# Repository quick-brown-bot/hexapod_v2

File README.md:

# Hexapod

An ESP32-powered hexapod robot built as a long-term robotics and embedded systems project.

The goal is not just to make a robot walk, but to learn and at the same time build a platform that is easy to experiment with, tune, and extend. Most robot behavior is configurable at runtime, control inputs are transport-independent, and the motion stack is organized into separated components.

The project combines firmware, hardware design, and system documentation in a single repository.

> 6 legs, 18 servos, ESP32 mainboard, distributed RP2040 leg controllers over
> an RS485 bus, per-servo current sensing.

This is a continuation of the original [Hexabot](https://github.com/quick-brown-bot/hexapod) project, developed here in
[`hexapod_v2`](https://github.com/quick-brown-bot/hexapod_v2). It differs from
the original mainly in electronics architecture — distributed RP2040 leg
controllers over RS485 instead of a single ESP32 driving all servos directly —
and adds new features such as per-servo current sensing.

---

## What Is In This Repository

The repository contains software and hardware assets used to develop and validate the robot.

```text
firmware/
├── mainboard/             ESP32 mainboard firmware (RS485 master)
├── leg/                   RP2040 leg controller firmware
└── mainboard_rs485_test/  Standalone RS485 bring-up/benchmark tool

hardware/
├── mainboard/             MainBoard schematic (ESP32 + IMU + RS485 master)
├── legboard/               LegBoard schematic (RP2040, servo PWM, current sensing)
└── powerboard/            MainPowerBoard schematic (battery, fusing, UBEC/SBEC)

docs/
├── architecture/          System architecture, hardware and mechanics
├── interfaces/            RS485, RPC, WiFi, Bluetooth, controller driver protocols
├── configuration/         Configuration platform design
├── development/           Build, flash, and dev workflow
└── plans/                 Project-wide backlog and research items
```

Mainboard firmware overview: [firmware/mainboard/README.md](firmware/mainboard/README.md)

The main firmware is built around a fixed 100 Hz control loop and a modular motion pipeline:

```text
Controller Input
        ↓
Gait Scheduler
        ↓
Foot Trajectory Generation
        ↓
Inverse Kinematics
        ↓
Motion Limiting
        ↓
Servo Outputs
```

---

## Current Technical Highlights

## Effort Summary

| Effort Area | Scope | Current Status | Notes |
| --- | --- | --- | --- |
| Locomotion Pipeline | Command mapping, gait scheduler, swing trajectory, whole-body IK | Implemented | Runs in a fixed 100 Hz control loop |
| KPP Motion Limits | Velocity, acceleration, jerk limiting and state estimation | Implemented | Runtime limits are configuration-backed |
| Controller Abstraction | Driver-agnostic core plus transport-specific drivers | Implemented | FlySky iBUS, Wi-Fi TCP, and Bluetooth Classic paths are present |
| RPC System | Queue-based command processing and config control | Implemented | Live inspection and runtime tuning are available |
| Configuration Platform | Namespace defaults, migration, discovery, persistence | Implemented | Core runtime namespaces are already consumed by modules |
| Configurator Tooling | External tuning and visualization UX | Planned | Firmware-side groundwork exists; UI work remains |

## Hardware Snapshot

- MCUs: ESP32 mainboard (FreeRTOS via ESP-IDF) + 6 × XIAO RP2040 (one per leg).
- Robot layout: 6 legs, 3 degrees of freedom per leg, 18 hobby servos total.
- Communication: RS485 multi-drop bus connecting the mainboard to all six leg controllers.
- Sensing: INA4181 4-channel current sensing per LegBoard for ground-contact detection.
- Power: dedicated MainPowerBoard with three UBECs (servo) and one SBEC (logic), fully isolated from logic power.
- Mechanical: custom 3D-printed chassis and leg parts.

## High-Level Architecture

```mermaid
flowchart LR
        Control[Controller stack]
        Config[RPC and config]
        App[Application loop]
        Loc[Locomotion]
        Limits[Motion limiting]
        Act[Actuation]
        Robot[Robot hardware]

        Control --> App
        Config --> App
        App --> Loc --> Limits --> Act --> Robot
        Config --> Control
```

- Controller stack: receives operator input from supported transports and normalizes it.
- RPC and config: handles runtime commands, parameter discovery, persistence, and save flows.
- Application loop: owns boot order and the 100 Hz control cycle.
- Locomotion: turns operator intent into gait phase, foot targets, and joint-space commands.
- Motion limiting: constrains commanded motion to configured dynamic envelopes.
- Actuation: maps joint commands to the PWM outputs that drive the robot.

### Runtime Configuration

Configuration is treated as a first-class subsystem rather than a collection of compile-time constants.

Parameters are organized into namespaces. Each namespace owns:

- parameter definitions,
- default values,
- validation rules,
- persistence behavior,
- migration logic,
- RPC discovery metadata.

The configuration manager provides:

- runtime parameter inspection,
- runtime modification,
- save/load operations,
- namespace registration,
- NVS persistence,
- version-aware migration support.

Robot geometry, calibration data, controller settings, motion limits, and other runtime behavior are loaded through this system rather than being hardcoded throughout the codebase.

### Motion Pipeline

The locomotion stack converts user commands into joint targets through a sequence of dedicated subsystems:

- gait scheduling,
- swing trajectory generation,
- inverse kinematics,
- velocity limiting,
- acceleration limiting,
- jerk limiting,
- servo actuation.

The motion loop runs at 100 Hz.

### Controller Abstraction

Controller transports are separated from locomotion.

Supported ingress paths currently include:

- FlySky iBUS,
- Wi-Fi TCP,
- Bluetooth Classic.

Each transport driver translates incoming data into a normalized controller state consumed by the motion system.

This allows locomotion, gait generation, and motion limiting to remain independent of transport-specific protocols.

### Hardware-Aware Design

The robot uses 18 servos arranged as three joints per leg:

- Coxa
- Femur
- Tibia

Servo signal generation is implemented on ESP32 using a combination of MCPWM and LEDC peripherals to fit within available hardware resources.

Power for logic and servos is separated to improve stability under heavy load.

---

## Engineering Problems Being Explored

This project is primarily a learning and engineering platform.

Current focus areas include:

- real-time control on resource-constrained hardware,
- gait generation and scheduling,
- inverse kinematics,
- motion smoothing and trajectory constraints,
- configuration architecture for embedded systems,
- transport-independent control interfaces,
- robotics software maintainability,
- practical servo-driven locomotion.

---

## Hardware Architecture

Distributed leg controllers with full separation of logic and servo power. The
architecture is defined and schematics are authored; firmware is in development.

- **Three boards**: MainBoard (ESP32 + IMU + RS485 master), LegBoard × 6 (XIAO
  RP2040, servo PWM, per-servo current sensing), MainPowerBoard (battery,
  fusing, UBEC/SBEC distribution).
- **The ESP32 does not generate servo PWM.** Joint commands are sent over RS485;
  each RP2040 generates PWM locally and interpolates between targets.
- **Per-servo current sensing** on every LegBoard enables ground-contact
  detection from current spikes without dedicated force sensors.
- **Servo current is fully isolated from the MainBoard** at the hardware level.

See [`docs/architecture/`](docs/architecture/) for the full architecture and interface documentation.

---

## Documentation

The repository contains detailed documentation covering implementation details and architecture decisions.

- [docs/architecture/SYSTEM_ARCHITECTURE.md](docs/architecture/SYSTEM_ARCHITECTURE.md)
- [docs/architecture/HARDWARE_AND_MECHANICS.md](docs/architecture/HARDWARE_AND_MECHANICS.md)
- [docs/interfaces/RS485_PROTOCOL.md](docs/interfaces/RS485_PROTOCOL.md)
- [docs/development/README.md](docs/development/README.md)
- [docs/interfaces/RPC_USER_GUIDE.md](docs/interfaces/RPC_USER_GUIDE.md)
- [docs/configuration/CONFIGURATION_PERSISTENCE_DESIGN.md](docs/configuration/CONFIGURATION_PERSISTENCE_DESIGN.md)
- [firmware/mainboard/README.md](firmware/mainboard/README.md)

Full documentation index: [docs/README.md](docs/README.md)

---

## Project Status

The project is under active development.

Current work focuses on improving locomotion quality, refining control architecture boundaries, and preparing the next generation of leg electronics while keeping the existing robot operational as a test platform.

---

## License

This repository uses Apache License 2.0 for the mainboard firmware.

License file location: [LICENSE](LICENSE)

Include the following notice in derivative works:

```text
Copyright 2025 Pawel Grudzien

Licensed under the Apache License, Version 2.0 (the "License");
you may not use this file except in compliance with the License.
You may obtain a copy of the License at

    http://www.apache.org/licenses/LICENSE-2.0

Unless required by applicable law or agreed to in writing, software
distributed under the License is distributed on an "AS IS" BASIS,
WITHOUT WARRANTIES OR CONDITIONS OF ANY KIND, either express or implied.
See the License for the specific language governing permissions and
limitations under the License.
```

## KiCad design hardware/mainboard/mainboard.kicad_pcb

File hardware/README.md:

# Hexapod boards

Schematics for the [system architecture](../docs/architecture/SYSTEM_ARCHITECTURE.md):
distributed leg controllers with logic power separated from servo power.

Three boards:

| Board | Source | Role |
|-------|--------|------|
| [MainBoard](mainboard/) | [`mainboard_sch.py`](mainboard/mainboard_sch.py) | ESP32 + IMU + RS485 master + 6× RJ11. Logic & comms only. |
| [LegBoard](legboard/) | [`legboard_sch.py`](legboard/legboard_sch.py) | XIAO RP2040 + SP3485 + 3 servos + sensing. One per leg. |
| [MainPowerBoard](powerboard/) | [`powerboard_sch.py`](powerboard/powerboard_sch.py) | Battery → fuse/switch/protection → 3 UBECs + SBEC → legs. |

There's also one bench-only tool, not part of the robot itself:

| Board | Source | Role |
|-------|--------|------|
| [calboard](calboard/) | [`calboard_sch.py`](calboard/calboard_sch.py) | XIAO RP2040 + resistor ladder. Plugs into a LegBoard's servo connectors in place of real servos to calibrate its current sensing — see [`firmware/calboard/README.md`](../firmware/calboard/README.md) and [`tools/current_calibration/`](../tools/current_calibration/). |

These schematics are authored **as code** with the
[`hardware-schematics`](schematic/README.md) toolchain. The Python script is
the source of truth; `uuids.json` is the committed UUID registry that protects
the PCB layout across regenerations. Edit the `.py`, never the `.kicad_sch` by
hand.

## Regenerating

```bash
python hardware/mainboard/mainboard_sch.py
python hardware/legboard/legboard_sch.py
python hardware/powerboard/powerboard_sch.py
```

Each writes its `<board>.kicad_sch` and updates `<board>/uuids.json` (additions
only for unchanged parts). `hardware/_common.py` resolves symbol libraries:
stock KiCad libs from the install (override with `KICAD_SYMBOL_DIR`), plus the
in-repo libraries under [`symbols/`](symbols/) — the Seeed XIAO series
(`Seeed_Studio_XIAO_Series.kicad_sym`), the ESP32 module (`SymbolsLib.kicad_sym`),
and `Hexapod_V2.kicad_sym` (flattened standalone `RJ25` and `SP3485CN`, because
the stock library defines those as derived `(extends …)` symbols the code
importer cannot follow).

The boards are self-contained: symbol libraries, footprints, and the FreeCAD
model live here under [`symbols/`](symbols/), [`footprints/`](footprints/) and
[`models/`](models/); they do not depend on any shared top-level libraries.

## Inter-board connections

```text
MainPowerBoard.J_LOGIC (+5V) ──► MainBoard.J7 (SBEC_5V_IN)
MainBoard.J1..J6 (RJ11)      ──► LegBoard.J1 (UPLINK_RJ11)        ×6
MainPowerBoard.J1..J6 (+6V)  ──► LegBoard.J5 (SERVO_PWR_IN)       ×6
```

### RJ11 / RJ25 leg link (MainBoard ↔ LegBoard)

The physical cable is populated as a 4-wire link inside a 6P6C/RJ25 shell, so
pins 1 and 6 are intentionally left unconnected.

| Pin | Net | Function |
|-----|-----|----------|
| 1 | — | unused |
| 2 | GND | Ground |
| 3 | RS485_A | RS485 A |
| 4 | RS485_B | RS485 B |
| 5 | +5V | Logic power |
| 6 | — | unused |

## MainBoard nets

| Net | Connects |
|-----|----------|
| `+5V` | SBEC input (J7), ESP32 dev-board VIN, all six RJ11 pin 5 |
| `+3.3V` | ESP32 dev-board 3V3 output, SP3485 VCC, IMU, decoupling, EN pull-up |
| `GND` | global ground |
| `ESP_TXD` / `ESP_RXD` | ESP32 IO17/IO16 (UART2) ↔ SP3485 DI/RO |
| `RS485_DE` | ESP32 IO4 → SP3485 DE + ~RE (direction) |
| `RS485_A` / `RS485_B` | SP3485 A/B ↔ all six RJ11, 120 Ω term (R1) |
| `IMU_SDA` / `IMU_SCL` / `IMU_INT` | ESP32 IO21/IO22/IO34 ↔ IMU header (J9) |

MainBoard decoupling intent (implemented in schematic code): `C1` 10 uF on +5V at
power entry (close to J7/U1 VIN), `C2` 100 nF at ESP32 3V3 pins, `C3` 100 nF at
SP3485 VCC, `C4` 100 nF at IMU header power pins, and `C5` 10 uF bulk on +3.3V
near the ESP32 3V3-source/load hub.

IMU header J9 (`Conn_01x05`): 1 = +3.3V, 2 = GND, 3 = SDA, 4 = SCL, 5 = INT.

Footprints currently driven from the generator: `U1` uses
`Custom:ESP32_Dev_Board`, `J1..J6` use
`Connector_RJ:RJ25_Wayconn_MJEA-660X1_Horizontal`, `J9` uses
`Connector_PinHeader_2.54mm:PinHeader_1x05_P2.54mm_Vertical`, `U2` uses the
SOIC-8 SP3485 footprint, and the ordinary small R/C parts default to 0805.

## LegBoard nets

| Net | Connects |
|-----|----------|
| `+5V` | RJ11 pin 5 logic power → XIAO VBUS (U1.14) |
| `+3.3V` | XIAO 3V3 out (U1.12) → SP3485 VCC, INA4181 VCC, decoupling |
| `+6V` | post-total-shunt servo bus; high-side **force** node feeding the three per-servo branch shunts and bulk cap C2 |
| `+6V_IN` | raw servo-power input (J5) ahead of the total shunt |
| `+6V_COXA` / `+6V_FEMUR` / `+6V_TIBIA` | post-branch-shunt servo supply rails (force) for J2 / J3 / J4 |
| `ITOT_SP` / `ITOT_SN` | Kelvin **sense** taps of total shunt R4 → INA IN+1 / IN-1 |
| `COXA_SP` / `COXA_SN` | Kelvin sense taps of coxa shunt R5 → INA IN+4 / IN-4 |
| `FEMUR_SP` / `FEMUR_SN` | Kelvin sense taps of femur shunt R3 → INA IN+2 / IN-2 |
| `TIBIA_SP` / `TIBIA_SN` | Kelvin sense taps of tibia shunt R2 → INA IN+3 / IN-3 |
| `GND` | global ground |
| `RP_TXD` / `RP_RXD` | XIAO P0/P1 (UART) ↔ SP3485 DI/RO |
| `RS485_DE` | XIAO P6/D4 → SP3485 DE + ~RE |
| `RS485_A` / `RS485_B` | SP3485 ↔ RJ11, 120 Ω term R1 (DNP except bus ends) |
| `COXA_PWM` / `FEMUR_PWM` / `TIBIA_PWM` | XIAO P3/P4/P2 → servo connectors J2/J3/J4 |
| `I_TOTAL_SENSE` | INA4181 channel 1 output → XIAO A0 |
| `I_FEMUR_SENSE` | INA4181 channel 2 output → XIAO A1 |
| `I_TIBIA_SENSE` | INA4181 channel 3 output → XIAO A2 |
| `I_COXA_SENSE` | INA4181 channel 4 output → XIAO A3 |

Servo connectors J2/J3/J4 (`Conn_01x03`): 1 = signal, 2 = branch +6V, 3 = GND.
J5 is a 2-pin screw terminal for servo power input. The four current shunts
`R2`/`R3`/`R4`/`R5` are **4-terminal (Kelvin) shunts** (`Device:R_Shunt`): pins
1/4 carry current, pins 2/3 are the sense taps. Each INA input reaches the shunt
over its own unique two-node `*_SP`/`*_SN` net, so the autorouter cannot merge
the three high-side taps (INA pins 6/15/17) through the shared `+6V` copper or
assign them current-rail trace widths. U3 (`INA4181A3IPWR`, gain 100) measures channel 1 across the total-leg shunt
`R4` (`+6V_IN`→`+6V`), channel 2 across femur `R3`, channel 3 across tibia
`R2`, channel 4 across coxa `R5`; IN+ is always on the higher-potential
(source) side. The generated sheet layout keeps the XIAO and INA
blocks as top-level anchors with the connector and power groups below for
readability.

> **Shunt placement must stay at rotation 0.** The schematic-as-code pin
> transform mismatches KiCad for off-axis pins at rotation 90/270 — the Kelvin
> sense pads land off the pin and the force pads swap. Verified via netlist
> export; keep the `Device:R_Shunt` placements un-rotated.

Footprints currently driven from the generator: `U1` uses
`Seeed_Studio_XIAO_Series:XIAO-RP2040-DIP`, `J1` uses
`Connector_RJ:RJ25_Wayconn_MJEA-660X1_Horizontal`, `U2` uses the SOIC-8
SP3485 footprint, `U3` uses `Custom:PW20_TEX`, `J2`/`J3`/`J4` use
`Connector_PinHeader_2.54mm:PinHeader_1x03_P2.54mm_Vertical`, `J5` uses
`TerminalBlock:TerminalBlock_MaiXu_MX126-5.0-02P_1x02_P5.00mm`, the four INA
shunts now use the 4-contact Kelvin footprint
`Resistor_SMD:R_Shunt_Ohmite_LVK12`, `C2` uses the through-hole radial candidate
`Capacitor_THT:CP_Radial_D8.0mm_P3.50mm` for an 8 mm diameter bulk capacitor, and
the ordinary small R/C parts default to 0805. Verify the LVK12 shunt power rating
and the capacitor lead pitch / body height against the exact parts before
freezing the PCB.

## MainPowerBoard nets

| Net | Connects |
|-----|----------|
| `BATT_RAW`→`BATT_FUSED`→`+VMAIN` | battery → F1 fuse → Q1/Q2 parallel PMOS reverse-polarity stage → main rail |
| `+VMAIN` | feeds the three UBEC modules (J8/J9/J10), the SBEC (J11), monitor (J13), bulk C4 |
| `VSERVO1` | UBEC1 out → legs 1,2 (J1,J2), bulk C1, LED D2 |
| `VSERVO2` | UBEC2 out → legs 3,4 (J3,J4), bulk C2, LED D3 |
| `VSERVO3` | UBEC3 out → legs 5,6 (J5,J6), bulk C3, LED D4 |
| `+5V` | SBEC out (J11) → logic output (J12), LED D5 |
| `GND` | global ground |

UBEC/SBEC module headers (`Conn_01x04`): 1 = +VMAIN in, 2 = GND, 3 = regulated
out, 4 = GND. Monitor header J13 (`Conn_01x05`): +VMAIN, VSERVO1, VSERVO2,
VSERVO3, GND.

`F1` is a soldered-in (non-replaceable) SMD fuse, Schurter 3413.0331.22
(20A, time-lag, 1206/`Fuse:Fuse_1206_3216Metric`) — chosen over an automotive
mini-blade holder because TME stocks no SMD blade-fuse holder; the previous
`Custom:Fuse Holder Mini` THT holder footprint is unused now but left in the
library.

Footprints currently driven from the generator: `J7` (battery input) uses
`Connector_Wire:SolderWire-1.5sqmm_1x02_P7.8mm_D1.7mm_OD3.9mm` solder pads,
`J1..J6` use
`TerminalBlock:TerminalBlock_MaiXu_MX126-5.0-02P_1x02_P5.00mm`, and `J13` uses
`Connector_PinHeader_2.54mm:PinHeader_1x05_P2.54mm_Vertical`. Bulk caps use
`C1..C3`: `Capacitor_THT:CP_Radial_D13.0mm_P5.00mm` (2200 uF class) and `C4`:
`Capacitor_THT:CP_Radial_D8.0mm_P3.80mm` (1000 uF class). The status resistor /
LED parts default to 0805. Reverse-polarity protection uses two parallel
`FQP47P06` PMOS parts in `Package_TO_SOT_THT:TO-220-3_Vertical`.

Power-entry control is now low-current at SW1: the high-current path is
`BATT_FUSED -> Q1/Q2 -> +VMAIN`, while SW1 only drives the PMOS gates through
`R7=10k` + `Q3` (NPN pull-down), with `R6=100k` pull-up and `R5=100R` series
gate resistor for damping.

Pre-prototype hardening now added in-code:
- `R8=100k` from `NPN_BASE` to `GND` (base pull-down; avoids floating base when SW1 is open).
- `D6=15V` Zener between `PMOS_GATE` and `BATT_FUSED` (Vgs transient clamp).
- Optional `C5=100nF` from `PMOS_GATE_DRV` to `GND` (slows turn-on edge to soften inrush into ~7600 uF total bulk capacitance).

## PCB order tagging

Each board order placed with JLCPCB is tagged in git at the exact commit that
was sent to manufacture:

```
git tag pcb_order_<JLCPCB-order-ID> <commit>
```

Example: `pcb_order_W2026062121528170` points to the first legboard/mainboard
order. To inspect or check out any ordered revision:

```bash
git show pcb_order_W2026062121528170          # view commit
git checkout pcb_order_W2026062121528170      # restore that state
```

This makes it possible to diff the current schematic against what was actually
fabricated, or to flash firmware that matches the physical board on hand.

---

## Status / known limitations (first pass)

These are deliberate module-abstraction simplifications to refine in Eeschema
before fabrication:

* **Reverse-polarity protection** now uses two parallel PMOS parts (`Q1`/`Q2`,
  `FQP47P06`) to leave thermal headroom for high current, plus a low-current
  gate-driver stage (`Q3`, `R5`, `R6`, `R7`, `R8`) so SW1 does not switch inrush
  current directly.
* **UBEC / SBEC / IMU / current sensor** are represented as module headers, not
  discrete designs.
* **ERC** loads cleanly but reports expected violations: unused ESP32/XIAO GPIO
  and the ESP32 `VIN`/`SENSOR_*` pins are left open (add no-connect flags), and
  off-grid endpoints (the loose auto-layout is meant to be re-placed in
  Eeschema). Net-label connectivity is verified correct via exported netlist.
* **Remaining footprint work** is limited to the high-current / bulk power-path
  parts and the placeholder module headers; the ordinary V2 passives, ESP32,
  XIAO RP2040, RJ25 connectors, and the IMU header are now assigned in code.

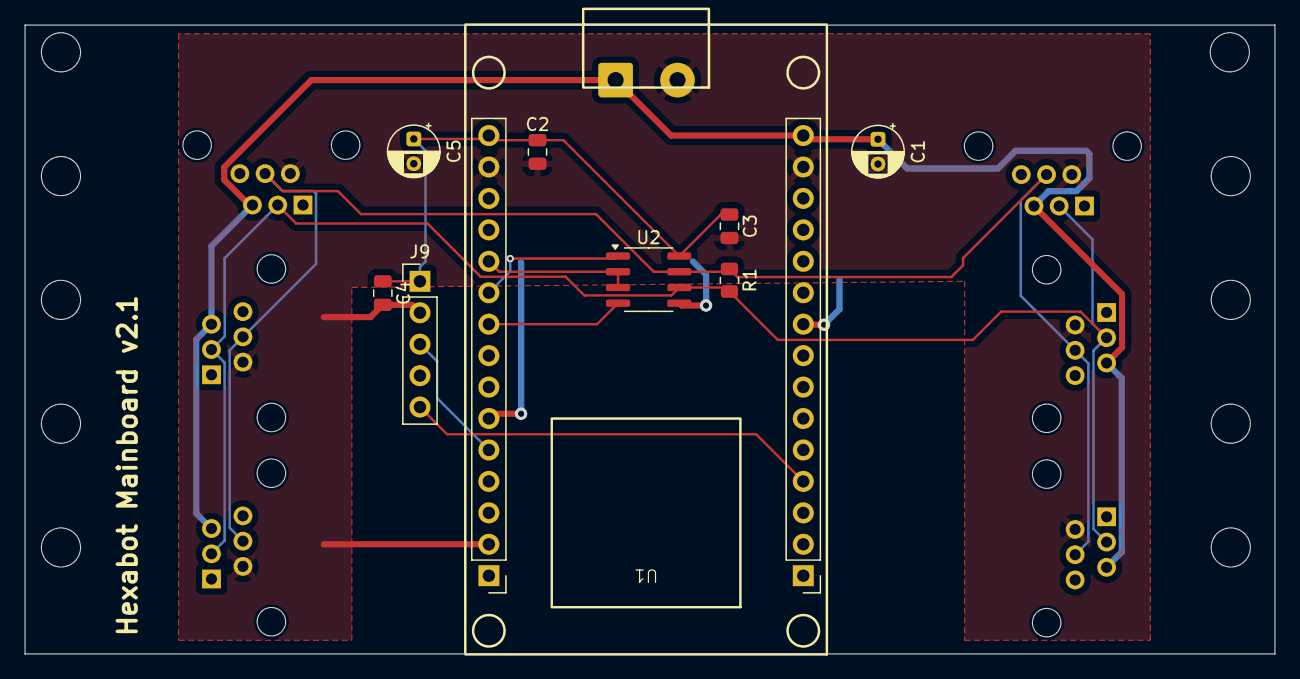
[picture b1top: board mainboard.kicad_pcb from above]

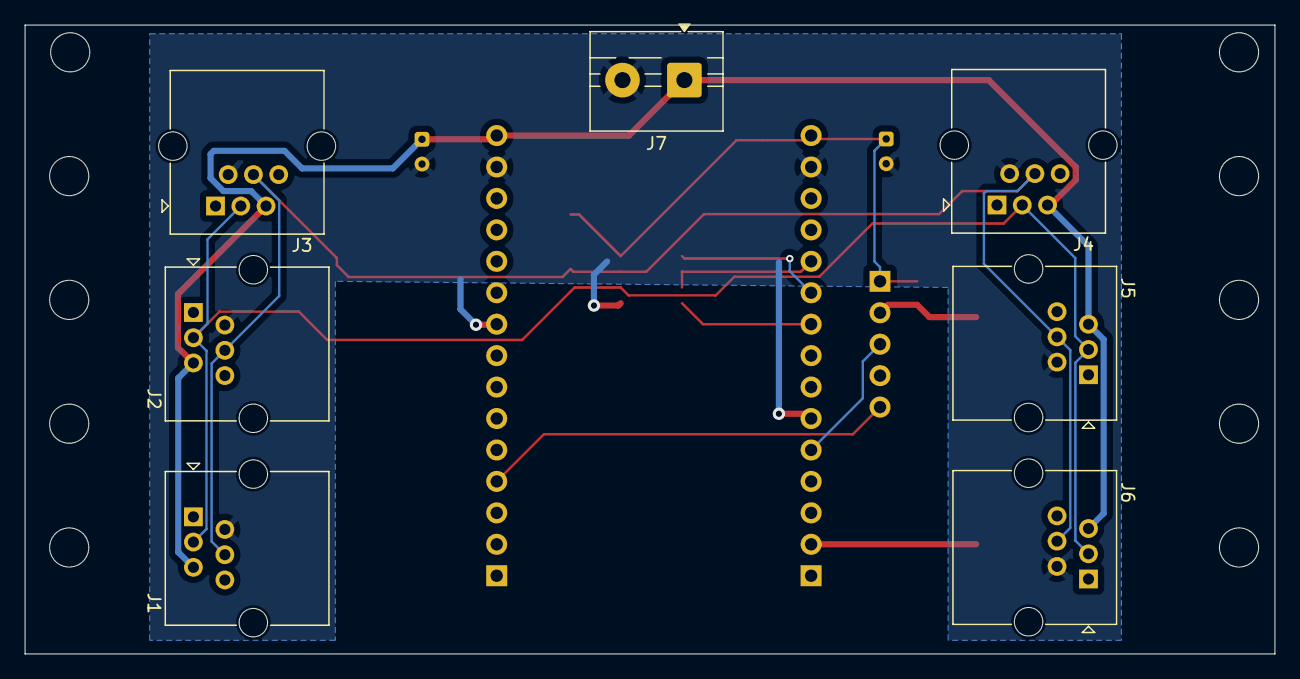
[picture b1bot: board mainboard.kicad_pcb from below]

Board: 2 copper layers, 101.0 x 50.8 mm, 16 parts (7 on the bottom side), 10 nets.

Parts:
C1, C5: 10uF; CP_Radial_D4.0mm_P2.00mm
C2, C3, C4: 100nF; C_0805_2012Metric
J1: LEG1_RJ11; RJ25_Wayconn_MJEA-660X1_Horizontal
J2: LEG2_RJ11; RJ25_Wayconn_MJEA-660X1_Horizontal
J3: LEG3_RJ11; RJ25_Wayconn_MJEA-660X1_Horizontal
J4: LEG4_RJ11; RJ25_Wayconn_MJEA-660X1_Horizontal
J5: LEG5_RJ11; RJ25_Wayconn_MJEA-660X1_Horizontal
J6: LEG6_RJ11; RJ25_Wayconn_MJEA-660X1_Horizontal
J7: SBEC_5V_IN; TerminalBlock_MaiXu_MX126-5.0-02P_1x02_P5.00mm
J9: IMU_I2C; PinHeader_1x05_P2.54mm_Vertical
R1: 120; R_0805_2012Metric
U1: ESP32-WROOM-32D; ESP32_Dev_Board
U2: SP3485CN; SOIC-8_3.9x4.9mm_P1.27mm

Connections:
+3.3V: C2.1, C3.1, C4.1, C5.1, J9.1, U1.3 (V3.3), U2.8 (VCC)
+5V: C1.1, J1.5, J2.5, J3.5, J4.5, J5.5, J6.5, J7.1, U1.2 (VIN)
ESP_RXD: U1.25 (IO16), U2.1 (RO)
ESP_TXD: U1.27 (IO17), U2.4 (DI)
GND: C1.2, C2.2, C3.2, C4.2, C5.2, J1.2, J2.2, J3.2, J4.2, J5.2, J6.2, J7.2, J9.2, U1.1 (GND), U1.15 (GND), U1.38 (GND), U1.39 (GND), U2.5 (GND)
IMU_INT: J9.5, U1.10 (IO34)
IMU_SDA: J9.3, U1.42 (IO21)
RS485_A: J1.3, J2.3, J3.3, J4.3, J5.3, J6.3, R1.2, U2.6 (A)
RS485_B: J1.4, J2.4, J3.4, J4.4, J5.4, J6.4, R1.1, U2.7 (B)
RS485_DE: U1.24 (IO4), U2.2 (~RE), U2.3 (DE)

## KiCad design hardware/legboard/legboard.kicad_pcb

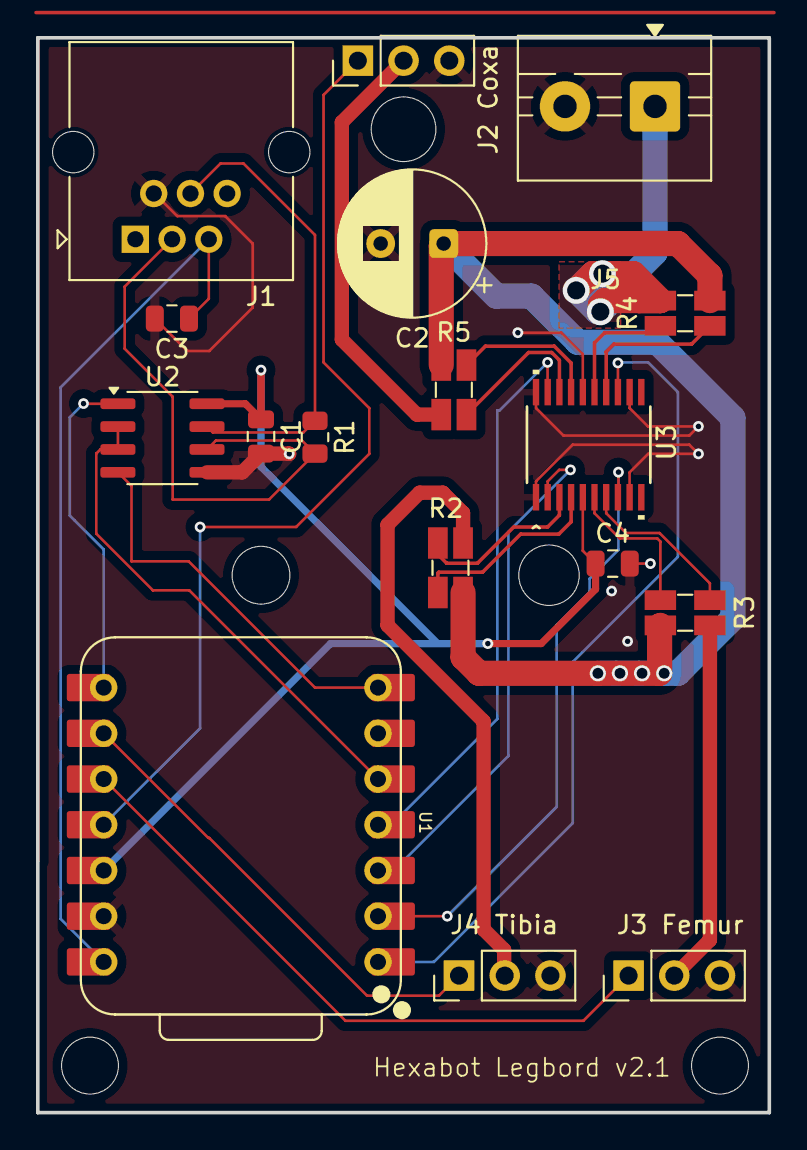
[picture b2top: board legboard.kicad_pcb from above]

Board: 2 copper layers, 40.6 x 59.7 mm, 17 parts (0 on the bottom side), 28 nets.

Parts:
C1, C3, C4: 100nF; C_0805_2012Metric
C2: 470uF; CP_Radial_D8.0mm_P3.50mm
J1: UPLINK_RJ11; RJ25_Wayconn_MJEA-660X1_Horizontal
J2 Coxa: COXA; PinHeader_1x03_P2.54mm_Vertical
J3 Femur: FEMUR; PinHeader_1x03_P2.54mm_Vertical
J4 Tibia: TIBIA; PinHeader_1x03_P2.54mm_Vertical
J5: SERVO_PWR_IN; TerminalBlock_MaiXu_MX126-5.0-02P_1x02_P5.00mm
R1: 120 (DNP); R_0805_2012Metric
R2, R3, R4, R5: 0.01; R_Shunt_Ohmite_LVK12
U1: XIAO-RP2040; XIAO-RP2040-DIP
U2: SP3485CN; SOIC-8_3.9x4.9mm_P1.27mm
U3: INA4181A3IPWR; PW20_TEX

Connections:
+3.3V: C1.1, C4.1, U1.12 (3V3), U2.8 (VCC), U3.5 (VS)
+5V: C3.1, J1.5, U1.14 (VBUS)
+6V: C2.1, R2.1, R3.1, R4.4, R5.1
+6V_COXA: J2 Coxa.2, R5.4
+6V_FEMUR: J3 Femur.2, R3.4
+6V_IN: J5.1, R4.1
+6V_TIBIA: J4 Tibia.2, R2.4
COXA_PWM: J2 Coxa.1, U1.11 (P3_D10_MOSI)
COXA_SN: R5.3, U3.18 (IN-4)
COXA_SP: R5.2, U3.17 (IN+4)
FEMUR_PWM: J3 Femur.1, U1.10 (P4_D9_MISO)
FEMUR_SN: R3.3, U3.7 (IN-2)
FEMUR_SP: R3.2, U3.6 (IN+2)
GND: C1.2, C2.2, C3.2, C4.2, J1.2, J2 Coxa.3, J3 Femur.3, J4 Tibia.3, J5.2, U1.13 (GND), U2.5 (GND), U3.1 (REF1), U3.9 (REF2), U3.12 (REF3), U3.16 (GND), U3.20 (REF4)
ITOT_SN: R4.3, U3.14 (IN-3)
ITOT_SP: R4.2, U3.15 (IN+3)
I_COXA_SENSE: U1.4 (P29_A3_D3), U3.19 (OUT4)
I_FEMUR_SENSE: U1.2 (P27_A1_D1), U3.8 (OUT2)
I_TIBIA_SENSE: U1.3 (P28_A2_D2), U3.2 (OUT1)
I_TOTAL_SENSE: U1.1 (P26_A0_D0), U3.13 (OUT3)
RP_RXD: U1.8 (P1_D7_RX), U2.1 (RO)
RP_TXD: U1.7 (P0_D6_TX), U2.4 (DI)
RS485_A: J1.3, R1.2, U2.6 (A)
RS485_B: J1.4, R1.1, U2.7 (B)
RS485_DE: U1.5 (P6_SDA_D4), U2.2 (~RE), U2.3 (DE)
TIBIA_PWM: J4 Tibia.1, U1.9 (P2_D8_SCK)
TIBIA_SN: R2.3, U3.3 (IN-1)
TIBIA_SP: R2.2, U3.4 (IN+1)

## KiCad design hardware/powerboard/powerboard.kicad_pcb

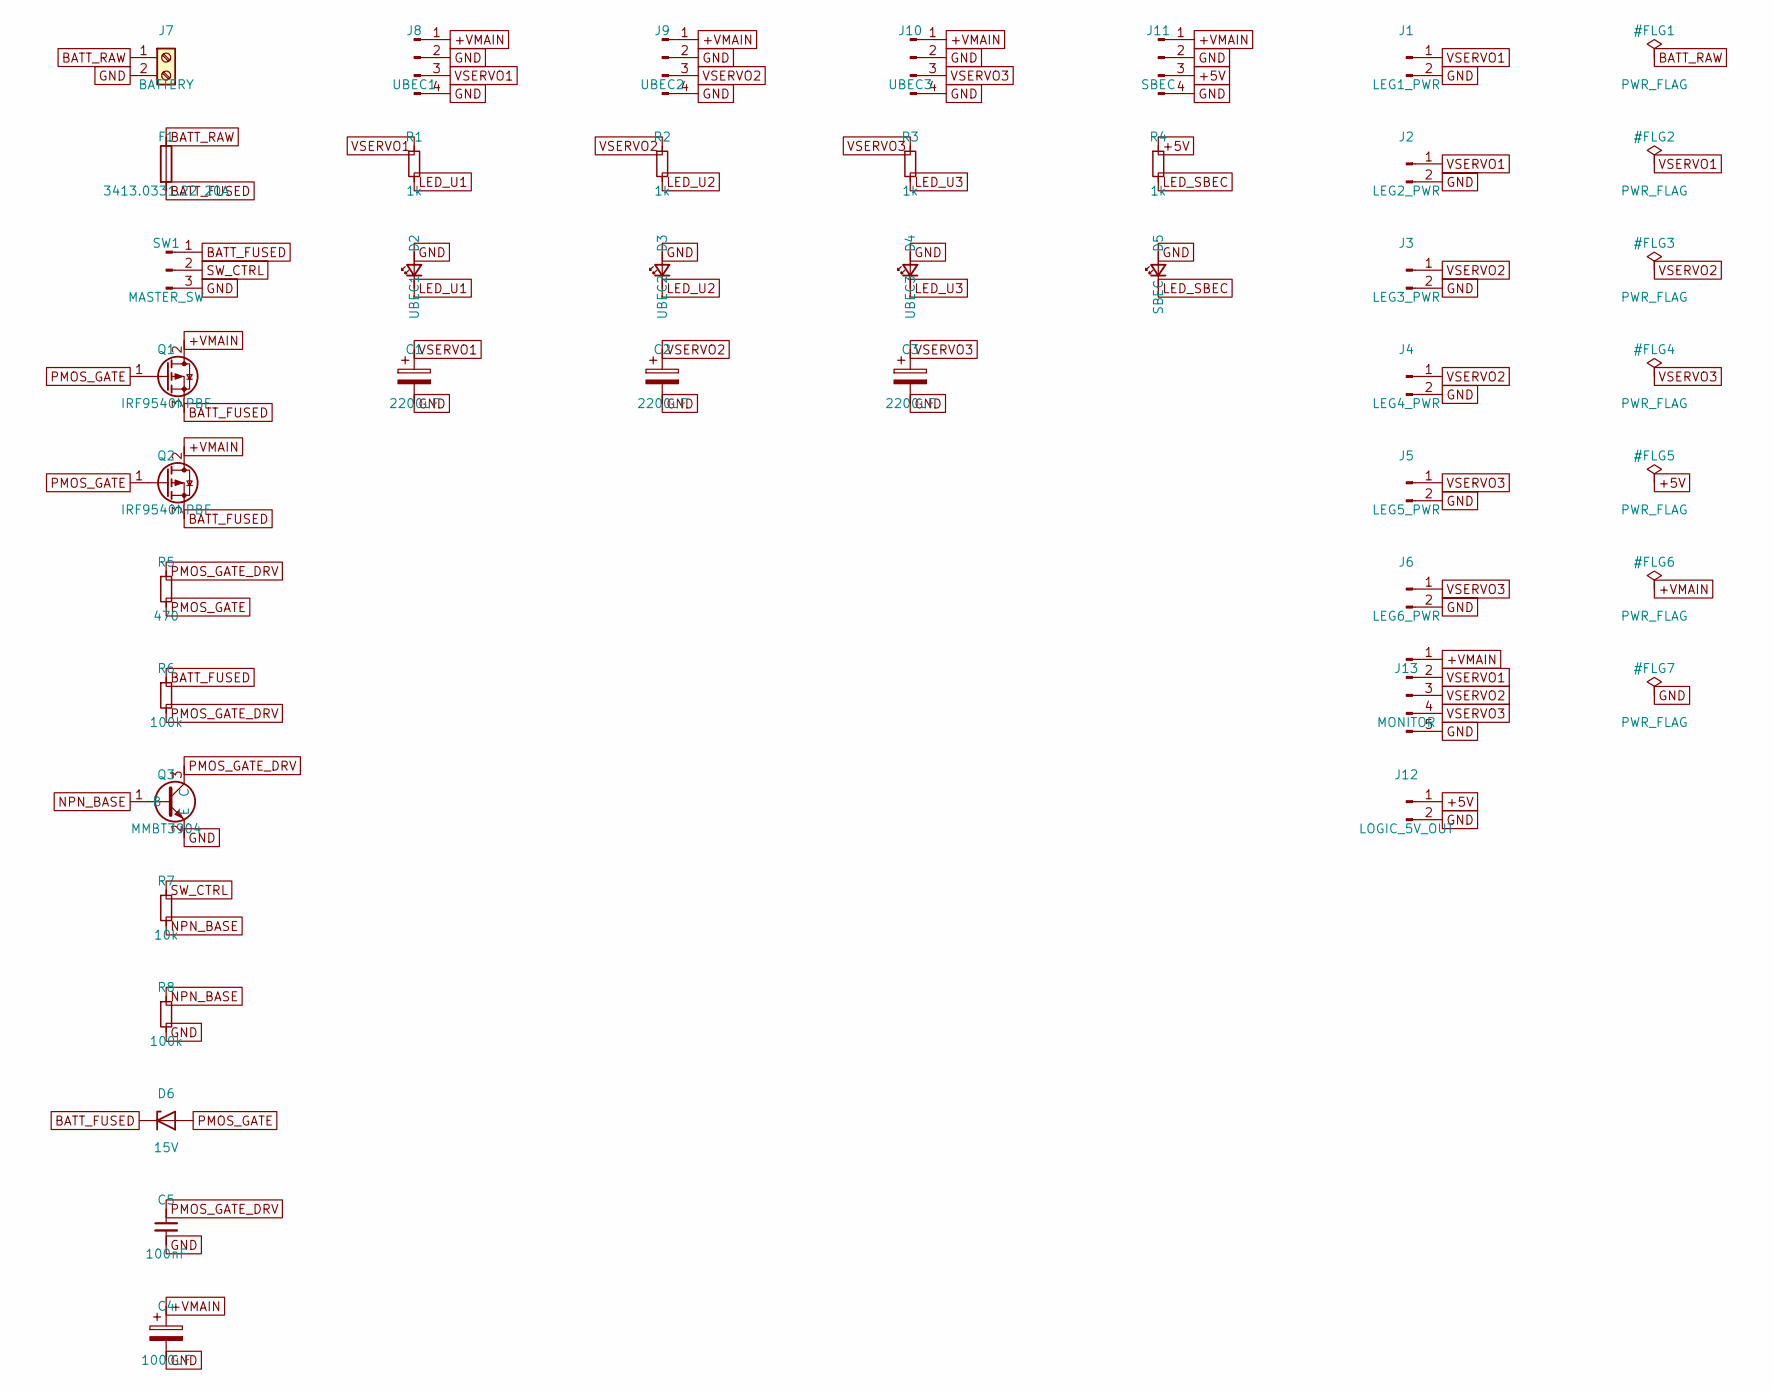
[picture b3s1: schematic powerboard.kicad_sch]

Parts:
C1, C2, C3: 2200uF; CP_Radial_D13.0mm_P5.00mm
C4: 1000uF; CP_Radial_D8.0mm_P3.80mm
C5: 100nF; C_0805_2012Metric
D2: UBEC1; LED_0805_2012Metric
D3: UBEC2; LED_0805_2012Metric
D4: UBEC3; LED_0805_2012Metric
D5: SBEC; LED_0805_2012Metric
D6: 15V; D_0805_2012Metric
F1: 3413.0331.22 20A; Fuse_1206_3216Metric
J1: LEG1_PWR; TerminalBlock_MaiXu_MX126-5.0-02P_1x02_P5.00mm
J2: LEG2_PWR; TerminalBlock_MaiXu_MX126-5.0-02P_1x02_P5.00mm
J3: LEG3_PWR; TerminalBlock_MaiXu_MX126-5.0-02P_1x02_P5.00mm
J4: LEG4_PWR; TerminalBlock_MaiXu_MX126-5.0-02P_1x02_P5.00mm
J5: LEG5_PWR; TerminalBlock_MaiXu_MX126-5.0-02P_1x02_P5.00mm
J6: LEG6_PWR; TerminalBlock_MaiXu_MX126-5.0-02P_1x02_P5.00mm
J7: BATTERY; SolderWire-1.5sqmm_1x02_P7.8mm_D1.7mm_OD3.9mm
J8: UBEC1; SolderWirePad_4x01_SMD_3x4mm
J9: UBEC2; SolderWirePad_4x01_SMD_3x4mm
J10: UBEC3; SolderWirePad_4x01_SMD_3x4mm
J11: SBEC; SolderWirePad_4x01_SMD_3x4mm
J12: LOGIC_5V_OUT; PinHeader_1x02_P2.54mm_Vertical
J13: MONITOR; PinHeader_1x05_P2.54mm_Vertical
Q1, Q2: IRF9540NPBF; TO-220-3_Vertical
Q3: MMBT3904; SOT-23
R1, R2, R3, R4: 1k; R_0805_2012Metric
R5: 470; R_0805_2012Metric
R6, R8: 100k; R_0805_2012Metric
R7: 10k; R_0805_2012Metric
SW1: MASTER_SW; SW_Slide_SPDT_Straight

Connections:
+5V: J11.3, J12.1, R4.1
+VMAIN: C4.1, J8.1, J9.1, J10.1, J11.1, J13.1, Q1.2 (D), Q2.2 (D)
BATT_FUSED: D6.1 (K), F1.2, Q1.3 (S), Q2.3 (S), R6.1, SW1.1
BATT_RAW: F1.1, J7.1
GND: C1.2, C2.2, C3.2, C4.2, C5.2, D2.2 (A), D3.2 (A), D4.2 (A), D5.2 (A), J1.2, J2.2, J3.2, J4.2, J5.2, J6.2, J7.2, J8.2, J8.4, J9.2, J9.4, J10.2, J10.4, J11.2, J11.4, J12.2, J13.5, Q3.2 (E), R8.2, SW1.3
LED_SBEC: D5.1 (K), R4.2
LED_U1: D2.1 (K), R1.2
LED_U2: D3.1 (K), R2.2
LED_U3: D4.1 (K), R3.2
NPN_BASE: Q3.1 (B), R7.2, R8.1
PMOS_GATE: D6.2 (A), Q1.1 (G), Q2.1 (G), R5.2
PMOS_GATE_DRV: C5.1, Q3.3 (C), R5.1, R6.2
SW_CTRL: R7.1, SW1.2
VSERVO1: C1.1, J1.1, J2.1, J8.3, J13.2, R1.1
VSERVO2: C2.1, J3.1, J4.1, J9.3, J13.3, R2.1
VSERVO3: C3.1, J5.1, J6.1, J10.3, J13.4, R3.1

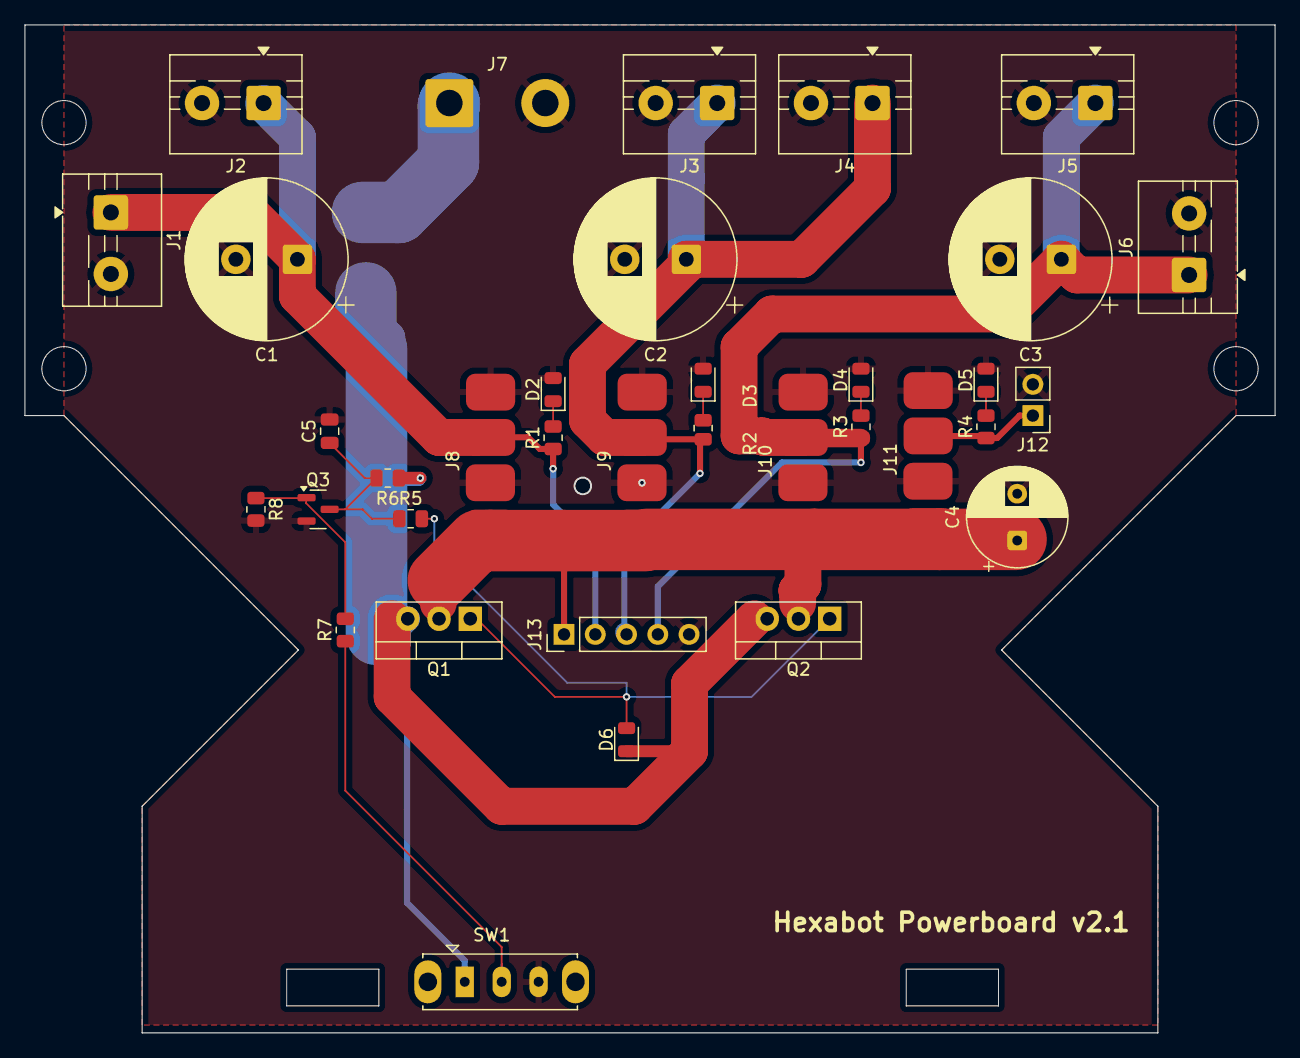
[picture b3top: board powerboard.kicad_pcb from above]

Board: 2 copper layers, 101.6 x 81.9 mm, 36 parts (1 on the bottom side), 16 nets.

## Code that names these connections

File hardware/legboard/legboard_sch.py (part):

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    sch.net("+5V", [u1.pin("14")])       # VBUS <- RJ11 logic power
    sch.net("+3.3V", [u1.pin("12")])     # 3V3 OUT (on-board regulator)
    sch.net("GND", [u1.pin("13")])
    sch.net("RP_TXD", [u1.pin("7")], rotation=180)     # P0/D6/TX -> RS485 DI
    sch.net("RP_RXD", [u1.pin("8")])     # P1/D7/RX <- RS485 RO
    sch.net("RS485_DE", [u1.pin("5")], rotation=180)   # P6/D4 -> driver enable
    sch.net("COXA_PWM", [u1.pin("11")])  # P3/D10
    sch.net("FEMUR_PWM", [u1.pin("10")])  # P4/D9
    sch.net("TIBIA_PWM", [u1.pin("9")])  # P2/D8
    sch.net("I_TOTAL_SENSE", [u1.pin("1")], rotation=180)    # P26/A0 (ADC)
    sch.net("I_FEMUR_SENSE", [u1.pin("2")], rotation=180)    # P27/A1 (ADC)
    sch.net("I_TIBIA_SENSE", [u1.pin("3")], rotation=180)    # P28/A2 (ADC)
    sch.net("I_COXA_SENSE", [u1.pin("4")], rotation=180)     # P29/A3 (ADC)

    # --- RS485 slave ------------------------------------------------------ #
    u2 = sch.place("Hexapod_V2:SP3485CN", "U2", at=(145, 72), value="SP3485CN",
                   footprint=SP3485_SOIC8_FOOTPRINT)
    sch.net("+3.3V", [u2.pin("8")])      # VCC
    sch.net("GND", [u2.pin("5")])
    sch.net("RP_RXD", [u2.pin("1")], rotation=180)     # RO
    sch.net("RP_TXD", [u2.pin("4")], rotation=180)     # DI
    sch.net("RS485_DE", [u2.pin("2"), u2.pin("3")], rotation=180)  # ~RE + DE tied
    sch.net("RS485_A", [u2.pin("6")])
    sch.net("RS485_B", [u2.pin("7")])

    # Bus termination 120R — DNP except on the two electrical ends of the bus.
    rt = sch.place("Device:R_Small", "R1", at=(170, 72), value="120 (DNP)",
                   rotation=90, footprint=RES_0805_FOOTPRINT)
    sch.net("RS485_A", [rt.pin("1")])
    sch.net("RS485_B", [rt.pin("2")])

    # --- RJ11 uplink: pins 1 and 6 intentionally unused ------------------ #
    j1 = sch.place("Hexapod_V2:RJ25", "J1", at=(25, 90), value="UPLINK_RJ11",
                   footprint=RJ25_FOOTPRINT)
    sch.net("GND", [j1.pin("2")])
    sch.net("RS485_A", [j1.pin("3")])
    sch.net("RS485_B", [j1.pin("4")])
    sch.net("+5V", [j1.pin("5")])

    # --- servo power input ------------------------------------------------ #
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                        footprint=SHUNT_R010_KELVIN_FOOTPRINT)
    sch.net("+6V_IN", [r_total.pin("1")])    # force, high side
    sch.net("+6V", [r_total.pin("4")])       # force, low side
    sch.net("ITOT_SP", [r_total.pin("2")])   # sense, high side -> IN+1
    sch.net("ITOT_SN", [r_total.pin("3")])   # sense, low side  -> IN-1

    # Branch shunts: current +6V (term 1) -> branch rail (term 4). The high-side
    # force pad stays on the shared +6V bulk; only the sense pads are per-branch.
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    # All four REF pins to GND (unidirectional, zero referenced to GND). Each IN+
    # is on the higher-potential (source) side of its shunt.
    stub_label("GND", u3.pin("1"), -15)            # REF1
    stub_label("I_TIBIA_SENSE", u3.pin("2"), -15)  # OUT1
    stub_label("TIBIA_SN", u3.pin("3"), -15)        # IN-1
    stub_label("TIBIA_SP", u3.pin("4"), -15)        # IN+1
    stub_label("+3.3V", u3.pin("5"), -15)          # VS
    stub_label("FEMUR_SP", u3.pin("6"), -15)        # IN+2
    stub_label("FEMUR_SN", u3.pin("7"), -15)        # IN-2
    stub_label("I_FEMUR_SENSE", u3.pin("8"), -15)   # OUT2
    stub_label("GND", u3.pin("9"), -15)             # REF2
    stub_label("GND", u3.pin("12"), 8)              # REF3
    stub_label("I_TOTAL_SENSE", u3.pin("13"), 8)    # OUT3
    stub_label("ITOT_SN", u3.pin("14"), 8)         # IN-3
    stub_label("ITOT_SP", u3.pin("15"), 8)         # IN+3
    stub_label("GND", u3.pin("16"), 8)              # GND
    stub_label("COXA_SP", u3.pin("17"), 8)          # IN+4
    stub_label("COXA_SN", u3.pin("18"), 8)          # IN-4
    stub_label("I_COXA_SENSE", u3.pin("19"), 8)     # OUT4
    stub_label("GND", u3.pin("20"), 8)             # REF4

    # --- decoupling / bulk ------------------------------------------------ #
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
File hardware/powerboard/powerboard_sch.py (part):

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    j_bat = sch.place("Connector:Screw_Terminal_01x02", "J7", at=(x1, y0),
                      value="BATTERY",
                      footprint=BATTERY_SOLDER_PADS_2P_FOOTPRINT)
    sch.net("BATT_RAW", [j_bat.pin("1")], rotation=180)
    sch.net("GND", [j_bat.pin("2")], rotation=180)

    f1 = sch.place("Device:Fuse", "F1", at=(x1, y1), value="3413.0331.22 20A",
                   footprint=FUSE_20A_FOOTPRINT)
    sch.net("BATT_RAW", [f1.pin("1")])
    sch.net("BATT_FUSED", [f1.pin("2")])

    sw1 = sch.place("Connector:Conn_01x03_Pin", "SW1", at=(x1, y2),
                    value="MASTER_SW", footprint=MASTER_SWITCH_FOOTPRINT)
    sch.net("BATT_FUSED", [sw1.pin("1")])
    sch.net("GND", [sw1.pin("3")])

    # Parallel PMOS reverse-polarity stage (shared source/drain/gate nets).
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                   footprint=PMOS_TO220_FOOTPRINT)
    q2 = sch.place("Transistor_FET:Q_PMOS_GDS", "Q2", at=(x1, y4), value="IRF9540NPBF",
                   footprint=PMOS_TO220_FOOTPRINT)
    sch.net("BATT_FUSED", [q1.pin("S"), q2.pin("S")])
    sch.net("+VMAIN", [q1.pin("D"), q2.pin("D")])

    # PMOS gate network: 100k pull-up to source rail and 470R series to gate bus.
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                   footprint=RES_0805_FOOTPRINT)
    r6 = sch.place("Device:R_Small", "R6", at=(x1, y6), value="100k",
                   footprint=RES_0805_FOOTPRINT)
    sch.net("PMOS_GATE_DRV", [r5.pin("1"), r6.pin("2")])
    sch.net("PMOS_GATE", [q1.pin("G"), q2.pin("G")], rotation=180)
    sch.net("PMOS_GATE", [r5.pin("2")])
    sch.net("BATT_FUSED", [r6.pin("1")])

    # NPN pull-down driver: collector to PMOS gate driver, emitter to GND,
    # base via 10k from switch output.
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                   footprint=RES_0805_FOOTPRINT)
    r8 = sch.place("Device:R_Small", "R8", at=(x1, y9), value="100k",
                   footprint=RES_0805_FOOTPRINT)
    sch.net("PMOS_GATE_DRV", [q3.pin("3")])
    sch.net("GND", [q3.pin("2")])
    sch.net("SW_CTRL", [sw1.pin("2"), r7.pin("1")])
    sch.net("NPN_BASE", [q3.pin("1")], rotation=180)
    sch.net("NPN_BASE", [r7.pin("2"), r8.pin("1")])
    sch.net("GND", [r8.pin("2")])

    # PMOS gate protection + optional inrush soft-start.
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                   footprint=DIODE_0805_FOOTPRINT)
    c5 = sch.place("Device:C_Small", "C5", at=(x1, y11), value="100nF",
                   footprint=CAP_0805_FOOTPRINT)
    sch.net("BATT_FUSED", [d6.pin("1")], rotation=180)
    sch.net("PMOS_GATE", [d6.pin("2")])
    sch.net("PMOS_GATE_DRV", [c5.pin("1")])
    sch.net("GND", [c5.pin("2")])

    c4 = sch.place("Device:C_Polarized", "C4", at=(x1, y12), value="1000uF",
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    d5 = sch.place("Device:LED_Small", "D5", at=(x5, y2), value="SBEC",
                   rotation=90, footprint=LED_0805_FOOTPRINT)
    sch.net("+5V", [r4.pin("1")])
    sch.net("LED_SBEC", [r4.pin("2"), d5.pin("2")])
    sch.net("GND", [d5.pin("1")])

    # --- logic output to MainBoard --------------------------------------- #
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    j_mon = sch.place("Connector:Conn_01x05_Pin", "J13", at=(x6, y6),
                      value="MONITOR", footprint=HEADER_1X05_THT_FOOTPRINT)
    sch.net("+VMAIN", [j_mon.pin("1")])
    sch.net("VSERVO1", [j_mon.pin("2")])
    sch.net("VSERVO2", [j_mon.pin("3")])
    sch.net("VSERVO3", [j_mon.pin("4")])
    sch.net("GND", [j_mon.pin("5")])

    # --- ERC power flags (battery source + module outputs) --------------- #
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
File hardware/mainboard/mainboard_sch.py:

"""Hexapod V2 — MainBoard schematic (source of truth).

Central logic + communication controller. Per the V2 architecture, this board
carries logic power, communication and control signals ONLY — never servo
current.

Contents:
* U1  ESP32-WROOM-32D — gait/IK/stabilisation/comms (the "intelligence").
* U2  SP3485CN RS485 transceiver — bus master to the six leg controllers.
* J7  SBEC logic-power input screw terminal from the MainPowerBoard (+5V).
* J_IMU  IMU breakout header (I2C + INT) — module abstraction, processed centrally.
* J1..J6 RJ11 (RJ25 6P used as 4-wire) leg interfaces: NC / GND / RS485 A /
    RS485 B / +5V logic / NC.
* C1  10uF THT bulk capacitor on +5V entry.
* C2  100nF local decoupling for ESP32 3V3.
* C3  100nF local decoupling for RS485 transceiver 3V3.
* C4  100nF local decoupling for IMU header 3V3.
* C5  10uF local bulk decoupling on +3.3V rail.

Power model: SBEC +5V comes in via screw terminal J7, is distributed unchanged
to the legs over RJ11 (logic power), and feeds the ESP32 dev board VIN. The
dev board's onboard regulator generates +3.3V, and that +3.3V pin powers the
IMU, RS485 transceiver and local decoupling network.

Run `python hardware/mainboard/mainboard_sch.py` to (re)generate
`mainboard.kicad_sch`. Connectivity is by net label; placement is a loose grid
meant to be tidied in Eeschema.

NOTE: unused ESP32 GPIO pins are left open here — add no-connect flags in
Eeschema before relying on ERC.
"""

from __future__ import annotations

import sys
from pathlib import Path

sys.path.insert(0, str(Path(__file__).resolve().parent.parent))  # hardware
from _common import (  # noqa: E402
    BULK_CAP_10UF_FOOTPRINT,
    CAP_0805_FOOTPRINT,
    ESP32_DEV_BOARD_FOOTPRINT,
    HEADER_1X05_THT_FOOTPRINT,
    RES_0805_FOOTPRINT,
    RJ25_FOOTPRINT,
    SCREW_TERMINAL_2P_FOOTPRINT,
    SP3485_SOIC8_FOOTPRINT,
    imp,
    power_flag,
)

from hardware.schematic import Schematic, UuidRegistry  # noqa: E402

HERE = Path(__file__).resolve().parent


def build() -> Schematic:
    reg = UuidRegistry(HERE / "uuids.json")
    sch = Schematic.new("mainboard", reg, paper="A4")

    imp(sch,
        "SymbolsLib:ESP32-WROOM-32D",
        "Hexapod_V2:SP3485CN",
        "Hexapod_V2:RJ25",
        "Connector:Conn_01x02_Pin",
        "Connector:Conn_01x05_Pin",
        "Device:R_Small",
        "Device:C_Small",
        "Device:C_Polarized")

    # --- main controller -------------------------------------------------- #
    u1 = sch.place("SymbolsLib:ESP32-WROOM-32D", "U1", at=(130, 55),
                   value="ESP32-WROOM-32D",
                   footprint=ESP32_DEV_BOARD_FOOTPRINT)
    sch.net("+5V", [u1.pin("2")])    # VIN
    sch.net("+3.3V", [u1.pin("V3.3")])
    sch.net("GND", [u1.pin("1")])
    sch.net("ESP_TXD", [u1.pin("IO17")])      # UART2 TX -> RS485 DI
    sch.net("ESP_RXD", [u1.pin("IO16")])      # UART2 RX <- RS485 RO
    sch.net("RS485_DE", [u1.pin("IO4")])      # driver enable / ~receiver enable
    sch.net("IMU_SDA", [u1.pin("IO21")])
    sch.net("IMU_SCL", [u1.pin("IO22")])
    sch.net("IMU_INT", [u1.pin("IO34")])

    # --- RS485 master ----------------------------------------------------- #
    u2 = sch.place("Hexapod_V2:SP3485CN", "U2", at=(195, 55), value="SP3485CN",
                   footprint=SP3485_SOIC8_FOOTPRINT)
    
    sch.net("+3.3V", [u2.pin("8")])     # VCC
    sch.net("GND", [u2.pin("5")])       # GND
    sch.net("ESP_RXD", [u2.pin("1")], rotation=180)                  # RO
    sch.net("ESP_TXD", [u2.pin("4")], rotation=180)                  # DI
    sch.net("RS485_DE", [u2.pin("2"), u2.pin("3")], rotation=180)    # ~RE + DE tied
    sch.net("RS485_A", [u2.pin("6")])
    sch.net("RS485_B", [u2.pin("7")])

    # Bus termination 100R across A/B (fit on the master end of the bus).
    rt = sch.place("Device:R_Small", "R1", at=(220, 95), value="100",
                   rotation=90, footprint=RES_0805_FOOTPRINT)
    sch.net("RS485_A", [rt.pin("1")])
    sch.net("RS485_B", [rt.pin("2")], rotation=180)

    # --- power input ----------------------------------------------------- #
    j_sbec = sch.place("Connector:Conn_01x02_Pin", "J7", at=(40, 90),
                       value="SBEC_5V_IN", footprint=SCREW_TERMINAL_2P_FOOTPRINT)
    sch.net("+5V", [j_sbec.pin("1")])
    sch.net("GND", [j_sbec.pin("2")])

    # --- IMU breakout (I2C) ---------------------------------------------- #
    j_imu = sch.place("Connector:Conn_01x05_Pin", "J9", at=(70, 120),
                      value="IMU_I2C", footprint=HEADER_1X05_THT_FOOTPRINT)
    sch.net("+3.3V", [j_imu.pin("1")])
    sch.net("GND", [j_imu.pin("2")])
    sch.net("IMU_SDA", [j_imu.pin("3")])
    sch.net("IMU_SCL", [j_imu.pin("4")])
    sch.net("IMU_INT", [j_imu.pin("5")])

    # --- decoupling ------------------------------------------------------- #
    # C1: place at the +5V entry cluster, physically close to J7 and U1 VIN.
    c1 = sch.place("Device:C_Polarized", "C1", at=(50, 110), value="10uF",
                   footprint=BULK_CAP_10UF_FOOTPRINT)
    sch.net("+5V", [c1.pin("1")])
    sch.net("GND", [c1.pin("2")])

    # C2: place immediately next to U1 3V3/GND pins (short return loop).
    c2 = sch.place("Device:C_Small", "C2", at=(150, 125), value="100nF",
                   footprint=CAP_0805_FOOTPRINT)
    sch.net("+3.3V", [c2.pin("1")])
    sch.net("GND", [c2.pin("2")])

    # C3: place immediately next to U2 VCC/GND pins.
    c3 = sch.place("Device:C_Small", "C3", at=(175, 125), value="100nF",
                   footprint=CAP_0805_FOOTPRINT)
    sch.net("+3.3V", [c3.pin("1")])
    sch.net("GND", [c3.pin("2")])

    # C4: place at the IMU header power pins (J9 pin 1/2).
    c4 = sch.place("Device:C_Small", "C4", at=(90, 125), value="100nF",
                   footprint=CAP_0805_FOOTPRINT)
    sch.net("+3.3V", [c4.pin("1")])
    sch.net("GND", [c4.pin("2")])

    # C5: place near the 3V3 source/load hub (between U1 3V3 and U2/IMU loads).
    c5 = sch.place("Device:C_Polarized", "C5", at=(115, 125), value="10uF",
                   footprint=BULK_CAP_10UF_FOOTPRINT)
    sch.net("+3.3V", [c5.pin("1")])
    sch.net("GND", [c5.pin("2")])

    # --- RJ11 leg interfaces (x6): pins 1 and 6 intentionally unused ----- #
    for i in range(1, 7):
        j = sch.place("Hexapod_V2:RJ25", f"J{i}", at=(40 + (i - 1) * 35, 155),
                      value=f"LEG{i}_RJ11", footprint=RJ25_FOOTPRINT)
        sch.net("GND", [j.pin("2")])
        sch.net("RS485_A", [j.pin("3")])
        sch.net("RS485_B", [j.pin("4")])
        sch.net("+5V", [j.pin("5")])

    # --- ERC power flags -------------------------------------------------- #
    power_flag(sch, "#FLG1", (40, 135), "+5V")
    power_flag(sch, "#FLG3", (80, 135), "GND")

    return sch


if __name__ == "__main__":
    build().write(HERE / "mainboard.kicad_sch")
    print("wrote mainboard.kicad_sch")
